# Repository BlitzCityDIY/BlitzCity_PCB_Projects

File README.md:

# BlitzCity_PCB_Projects
Projects with PCB files

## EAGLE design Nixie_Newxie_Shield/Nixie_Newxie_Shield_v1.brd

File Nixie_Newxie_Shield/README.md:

# Nixie Newxie Shield

A PCB that lets you plug four [Newxie Vertical Displays](https://www.adafruit.com/product/6113) into an Arduino/Metro format board.

It uses the 2x3 SPI pins on the edge of the board and pins 5-12 for CS and DC for each display.

Tested with an [Adafruit Metro ESP32-S3](https://www.adafruit.com/product/5500). Two Arduino examples are available:

* Color Test - Blinks a different color on each of the four displays (yellow, red, blue and green)
* Nixie Clock - Fetches the time from the [Worldtime API](http://worldtimeapi.org/api/timezone/Etc/UTC) and displays it using Nixie tube number images
	* The Nixie tube images are from [Wikimedia](https://commons.wikimedia.org/w/index.php?search=nixie+tube+Z566M&title=Special%3AMediaSearch&type=image). They were cropped, converted to bitmaps and converted to byte arrays with [image2cpp](https://javl.github.io/image2cpp/).

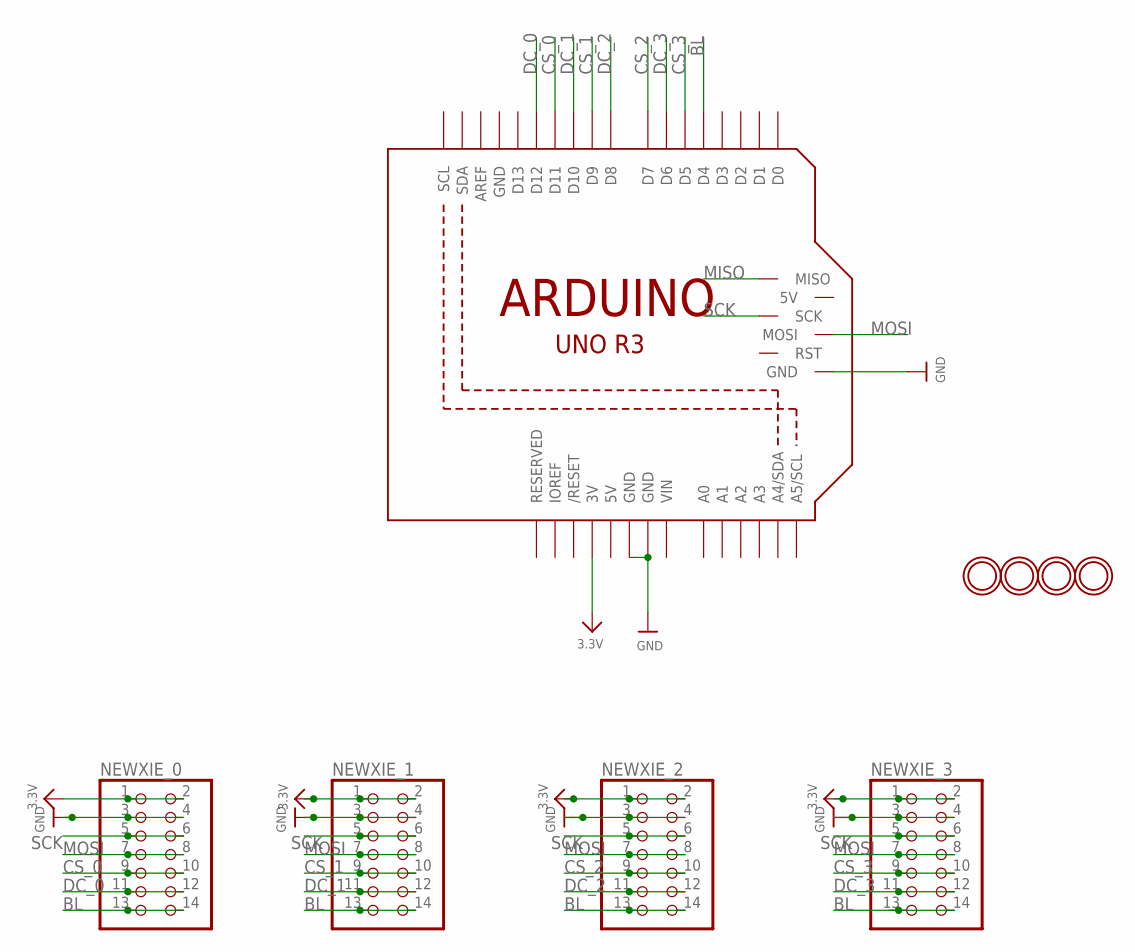
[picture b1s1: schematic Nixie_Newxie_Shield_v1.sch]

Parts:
NEWXIE_0, NEWXIE_1, NEWXIE_2, NEWXIE_3: HEADER-2X7; 2X07
U$12, U$13, U$14, U$15: MOUNTINGHOLE3.0_NPH; MOUNTINGHOLE_3.0_NPH
U$19: ARDUINO_R3_ICSP_NODIM; ARDUINOR3_ICSP_NODIM

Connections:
3.3V: NEWXIE_0.1, NEWXIE_0.2, NEWXIE_1.1, NEWXIE_1.2, NEWXIE_2.1, NEWXIE_2.2, NEWXIE_3.1, NEWXIE_3.2, U$19.3V
5V: U$19.5V
BL: NEWXIE_0.13, NEWXIE_0.14, NEWXIE_1.13, NEWXIE_1.14, NEWXIE_2.13, NEWXIE_2.14, NEWXIE_3.13, NEWXIE_3.14, U$19.D4
CS_0: NEWXIE_0.9, NEWXIE_0.10, U$19.D11
CS_1: NEWXIE_1.9, NEWXIE_1.10, U$19.D9
CS_2: NEWXIE_2.9, NEWXIE_2.10, U$19.D7
CS_3: NEWXIE_3.9, NEWXIE_3.10, U$19.D5
DC_0: NEWXIE_0.11, NEWXIE_0.12, U$19.D12
DC_1: NEWXIE_1.11, NEWXIE_1.12, U$19.D10
DC_2: NEWXIE_2.11, NEWXIE_2.12, U$19.D8
DC_3: NEWXIE_3.11, NEWXIE_3.12, U$19.D6
GND: NEWXIE_0.3, NEWXIE_0.4, NEWXIE_1.3, NEWXIE_1.4, NEWXIE_2.3, NEWXIE_2.4, NEWXIE_3.3, NEWXIE_3.4, U$19.GND, U$19.GND@1 (GND), U$19.GND@2 (GND), U$19.GND@3 (GND)
MISO: U$19.MISO
MOSI: NEWXIE_0.7, NEWXIE_0.8, NEWXIE_1.7, NEWXIE_1.8, NEWXIE_2.7, NEWXIE_2.8, NEWXIE_3.7, NEWXIE_3.8, U$19.MOSI
SCK: NEWXIE_0.5, NEWXIE_0.6, NEWXIE_1.5, NEWXIE_1.6, NEWXIE_2.5, NEWXIE_2.6, NEWXIE_3.5, NEWXIE_3.6, U$19.SCK
VIN: U$19.VIN

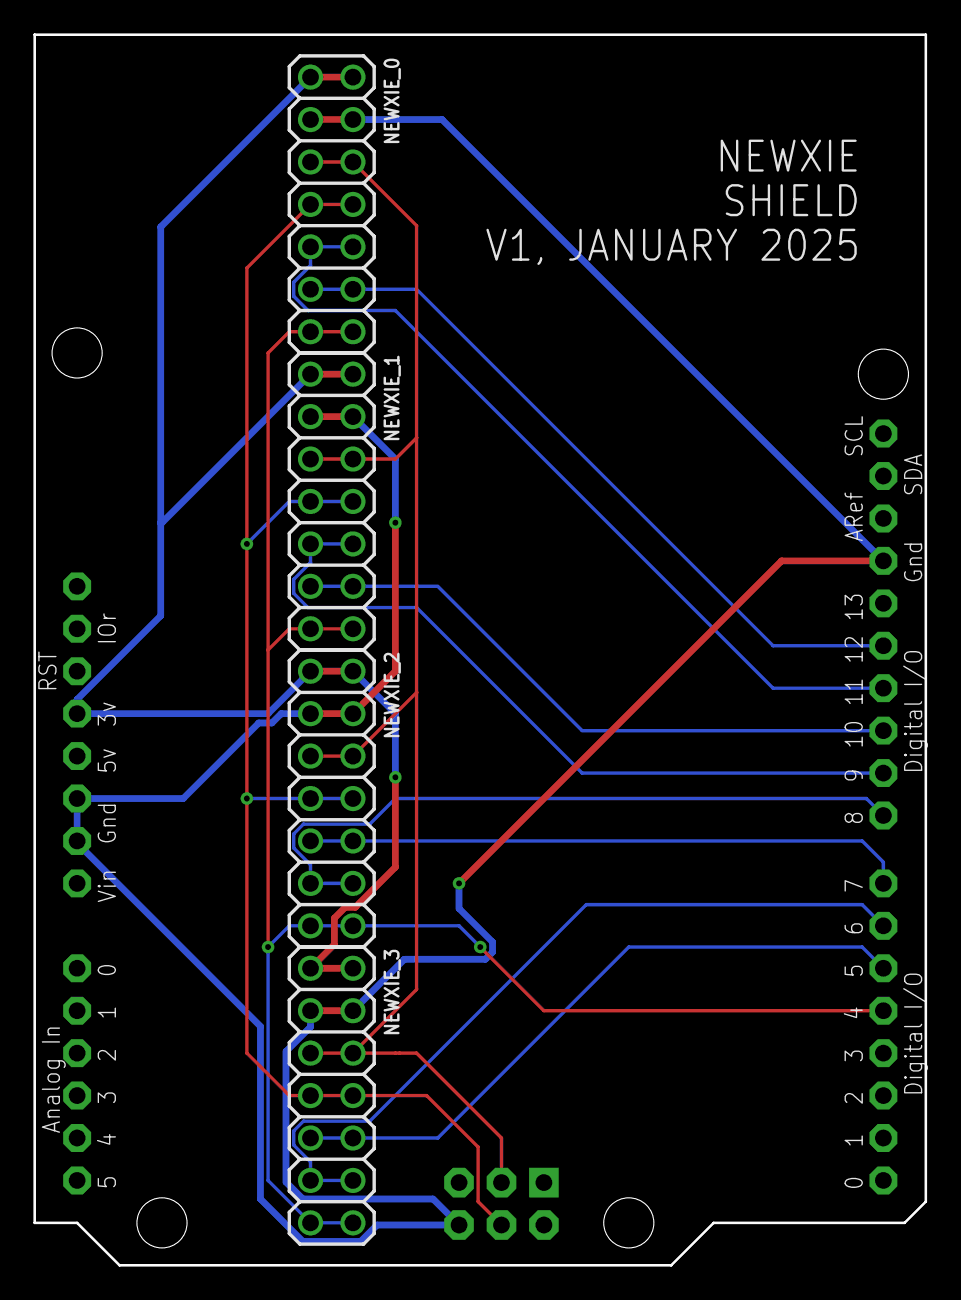
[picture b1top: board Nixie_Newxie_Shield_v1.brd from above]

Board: 2 copper layers, 53.3 x 73.7 mm, 9 parts (0 on the bottom side), 13 nets.

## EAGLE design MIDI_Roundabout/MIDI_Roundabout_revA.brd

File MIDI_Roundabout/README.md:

# MIDI Roundabout

A PCB that lets you route TRS-A, DIN-5 or TRS-B MIDI signals. It uses the MIDI Thru circuit with 220 ohm resistors on the two signal lines.

The switch is a [DP3T switch](https://www.digikey.com/en/products/detail/c-k/JS203011SCQN/7056055) that is available for PCBA on JLCPCB. The BOM and part placement files are available in the Gerber files folder.

Live demo video on [YouTube](https://www.youtube.com/live/Z-Sb5L-gl7c?si=7ahsuTD-HjMJuZga&t=2058)

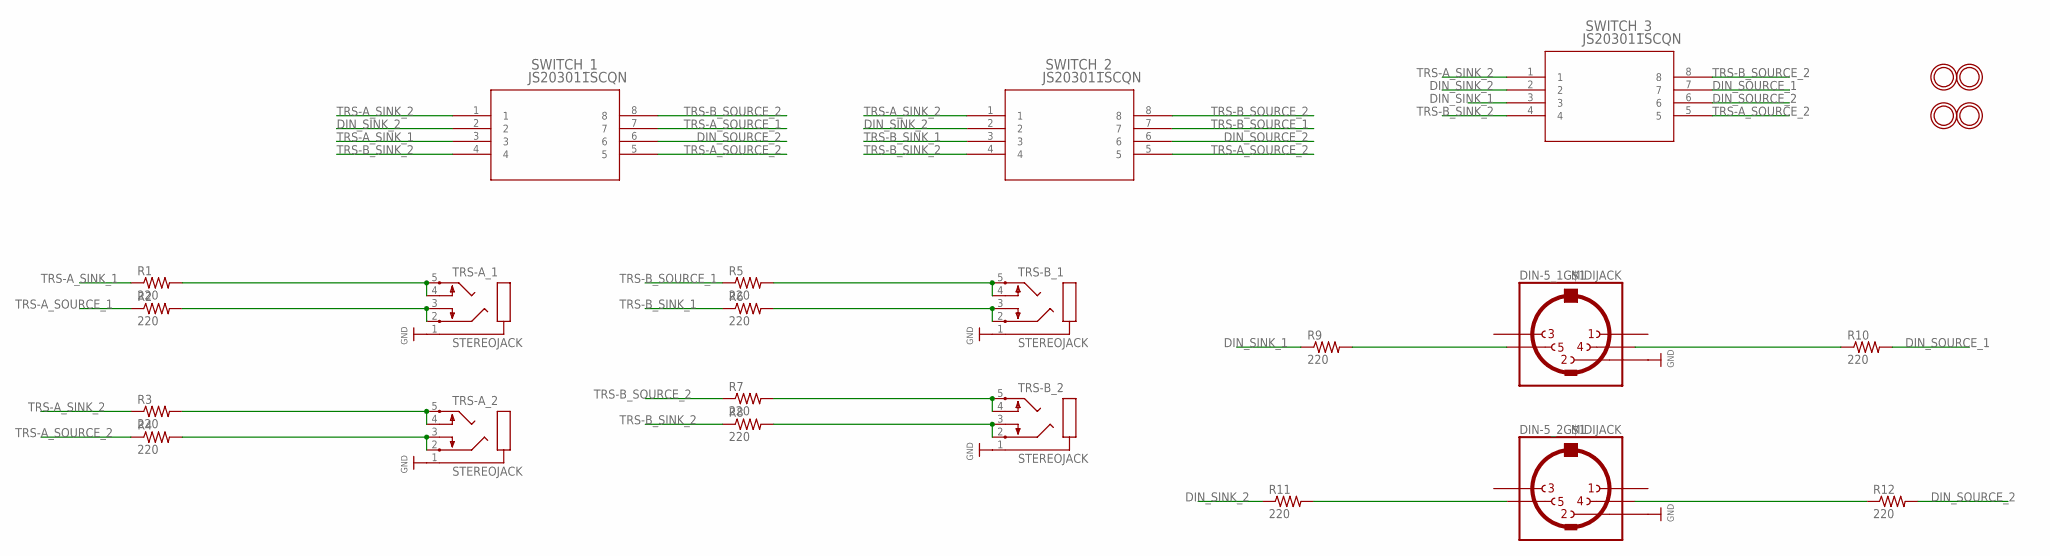
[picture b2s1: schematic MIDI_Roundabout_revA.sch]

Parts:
DIN-5_1, DIN-5_2: MIDIJACK; CP-2350
R1, R2, R3, R4, R5, R6, R7, R8, R9, R10, R11, R12: 220; R0805
SWITCH_1, SWITCH_2, SWITCH_3: JS203011SCQN; SWITCH_3011SCQN
TRS-A_1, TRS-A_2: STEREOJACK; STX3100
TRS-B_1, TRS-B_2: STEREOJACK; STX3100
U$7, U$8, U$9, U$10: MOUNTINGHOLE2.5_THICK; MOUNTINGHOLE_2.5_PLATED_THICK

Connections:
DIN_SINK_1: R9.1, SWITCH_3.3
DIN_SINK_2: R11.1, SWITCH_1.2, SWITCH_2.2, SWITCH_3.2
DIN_SOURCE_1: R10.2, SWITCH_3.7
DIN_SOURCE_2: R12.2, SWITCH_1.6, SWITCH_2.6, SWITCH_3.6
GND: DIN-5_1.2, DIN-5_2.2, TRS-A_1.1, TRS-A_2.1, TRS-B_1.1, TRS-B_2.1
unnamed: DIN-5_1.5, R9.2
unnamed: DIN-5_1.4, R10.1
unnamed: DIN-5_2.4, R12.1
unnamed: DIN-5_2.5, R11.2
unnamed: R1.2, TRS-A_1.4, TRS-A_1.5
unnamed: R2.2, TRS-A_1.2, TRS-A_1.3
unnamed: R3.2, TRS-A_2.4, TRS-A_2.5
unnamed: R4.2, TRS-A_2.2, TRS-A_2.3
unnamed: R5.2, TRS-B_1.4, TRS-B_1.5
unnamed: R6.2, TRS-B_1.2, TRS-B_1.3
unnamed: R7.2, TRS-B_2.4, TRS-B_2.5
unnamed: R8.2, TRS-B_2.2, TRS-B_2.3
TRS-A_SINK_1: R1.1, SWITCH_1.3
TRS-A_SINK_2: R3.1, SWITCH_1.1, SWITCH_2.1, SWITCH_3.1
TRS-A_SOURCE_1: R2.1, SWITCH_1.7
TRS-A_SOURCE_2: R4.1, SWITCH_1.5, SWITCH_2.5, SWITCH_3.5
TRS-B_SINK_1: R6.1, SWITCH_2.3
TRS-B_SINK_2: R8.1, SWITCH_1.4, SWITCH_2.4, SWITCH_3.4
TRS-B_SOURCE_1: R5.1, SWITCH_2.7
TRS-B_SOURCE_2: R7.1, SWITCH_1.8, SWITCH_2.8, SWITCH_3.8

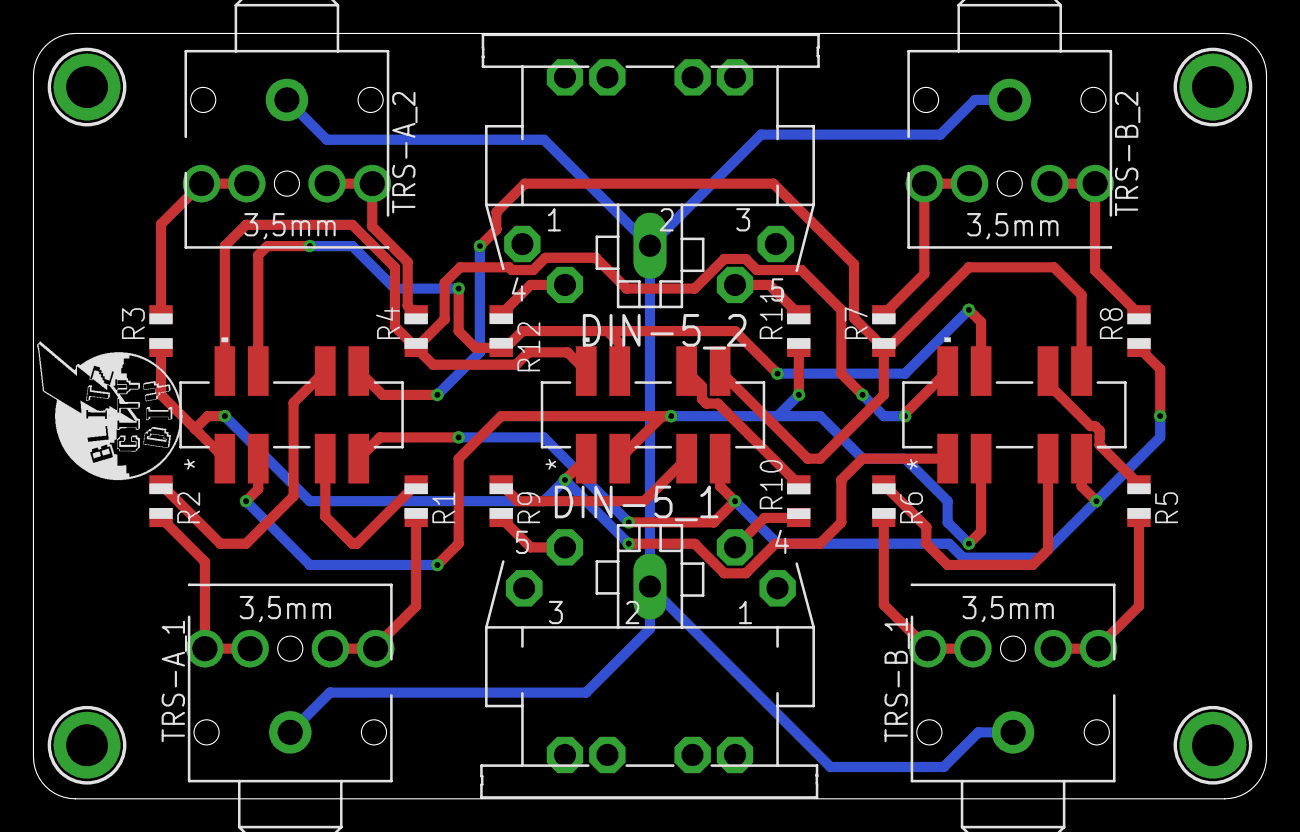
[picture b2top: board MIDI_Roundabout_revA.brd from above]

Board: 2 copper layers, 73.7 x 45.7 mm, 45 parts (0 on the bottom side), 25 nets.

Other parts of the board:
PLABEL200: PLABEL200
PLABEL201: PLABEL201
PLABEL202: PLABEL202
PLABEL203: PLABEL203
PLABEL204: PLABEL204
PLABEL205: PLABEL205
PLABEL206: PLABEL206
PLABEL207: PLABEL207
PLABEL208: PLABEL208
PLABEL209: PLABEL209
PLABEL210: PLABEL210
PLABEL211: PLABEL211
PLABEL212: PLABEL212
PLABEL213: PLABEL213
PLABEL214: PLABEL214
PLABEL215: PLABEL215
PLABEL216: PLABEL216
PLABEL217: PLABEL217
PLABEL218: PLABEL218
PLABEL219: PLABEL219

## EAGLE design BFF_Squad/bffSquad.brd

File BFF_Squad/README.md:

# BFF Squad

A carrier PCB that lets you use multiple QT Py BFF breakout boards with a QT Py without having to stack them vertically. 

This is a bit of a hack, make sure you check that the BFF's you're using aren't sharing important pins.

Shared on [OSHPark](https://oshpark.com/shared_projects/5sXhVjRq)

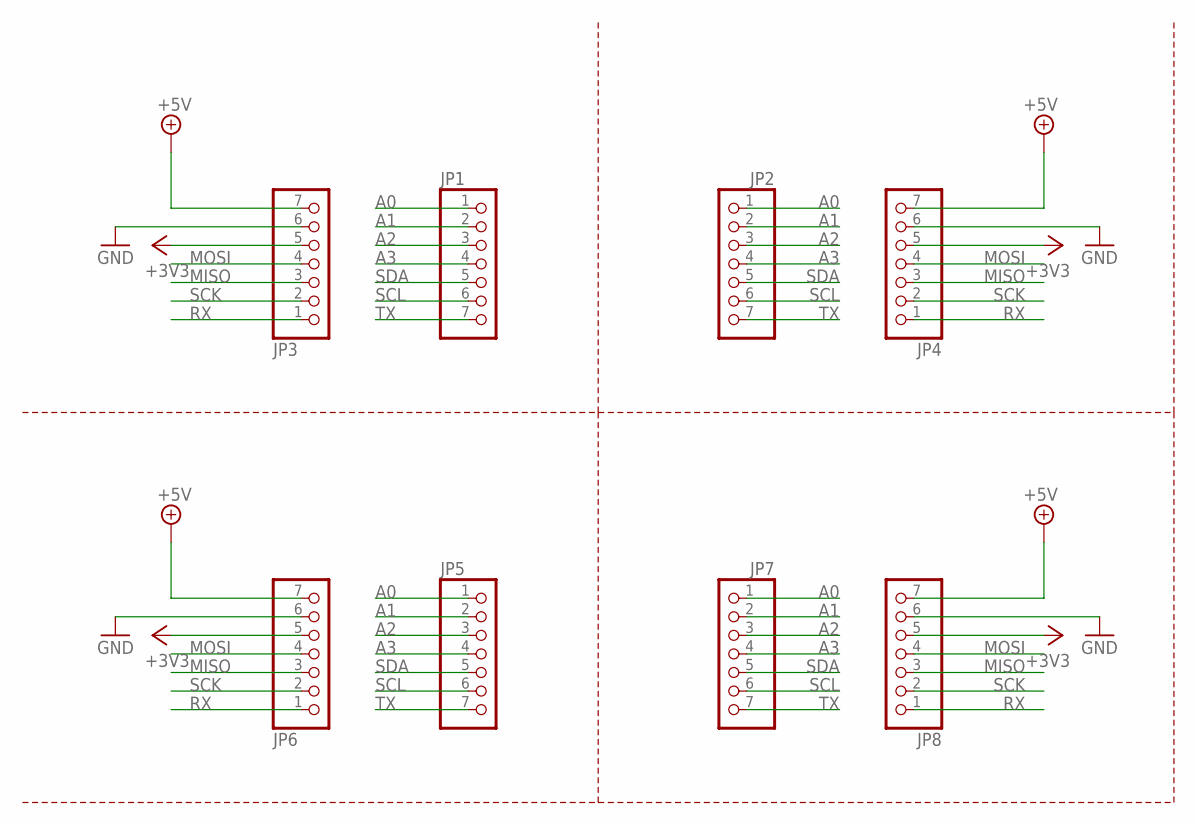
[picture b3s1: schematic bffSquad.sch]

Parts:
JP1, JP2, JP3, JP4, JP5, JP6, JP7, JP8: HEADER-1X7ROUND; 1X07_ROUND

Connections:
+3V3: JP3.5, JP4.5, JP6.5, JP8.5
+5V: JP3.7, JP4.7, JP6.7, JP8.7
A0: JP1.1, JP2.1, JP5.1, JP7.1
A1: JP1.2, JP2.2, JP5.2, JP7.2
A2: JP1.3, JP2.3, JP5.3, JP7.3
A3: JP1.4, JP2.4, JP5.4, JP7.4
GND: JP3.6, JP4.6, JP6.6, JP8.6
MISO: JP3.3, JP4.3, JP6.3, JP8.3
MOSI: JP3.4, JP4.4, JP6.4, JP8.4
RX: JP3.1, JP4.1, JP6.1, JP8.1
SCK: JP3.2, JP4.2, JP6.2, JP8.2
SCL: JP1.6, JP2.6, JP5.6, JP7.6
SDA: JP1.5, JP2.5, JP5.5, JP7.5
TX: JP1.7, JP2.7, JP5.7, JP7.7

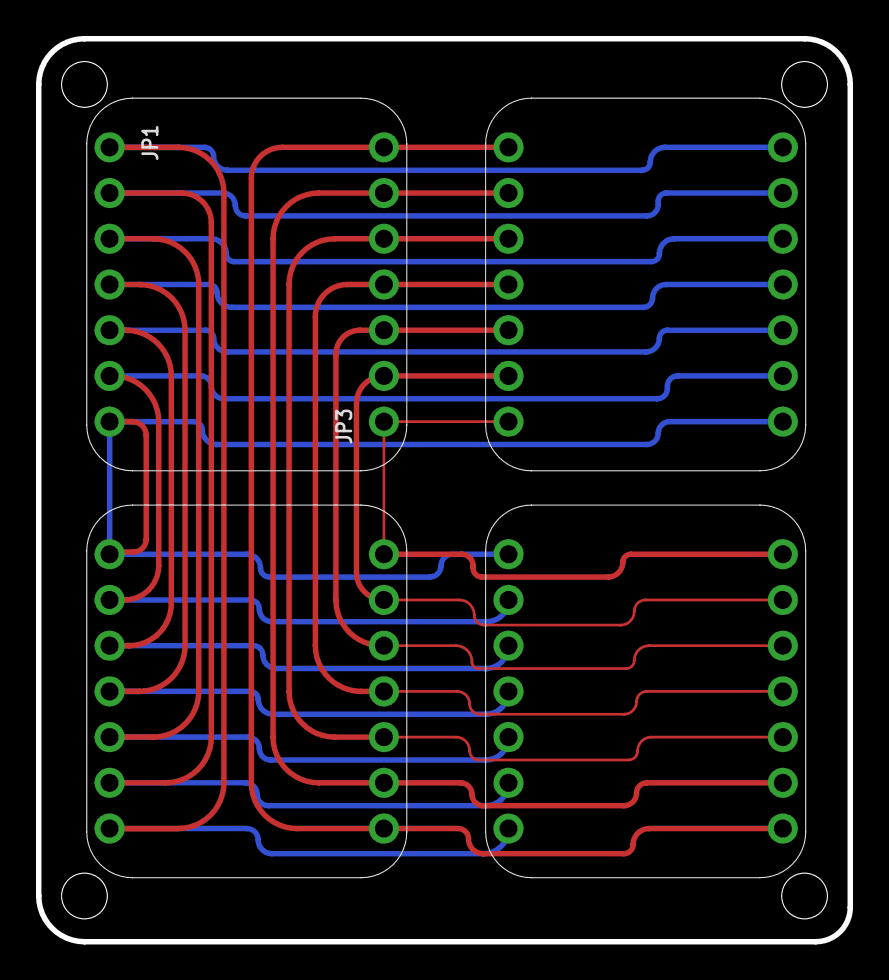
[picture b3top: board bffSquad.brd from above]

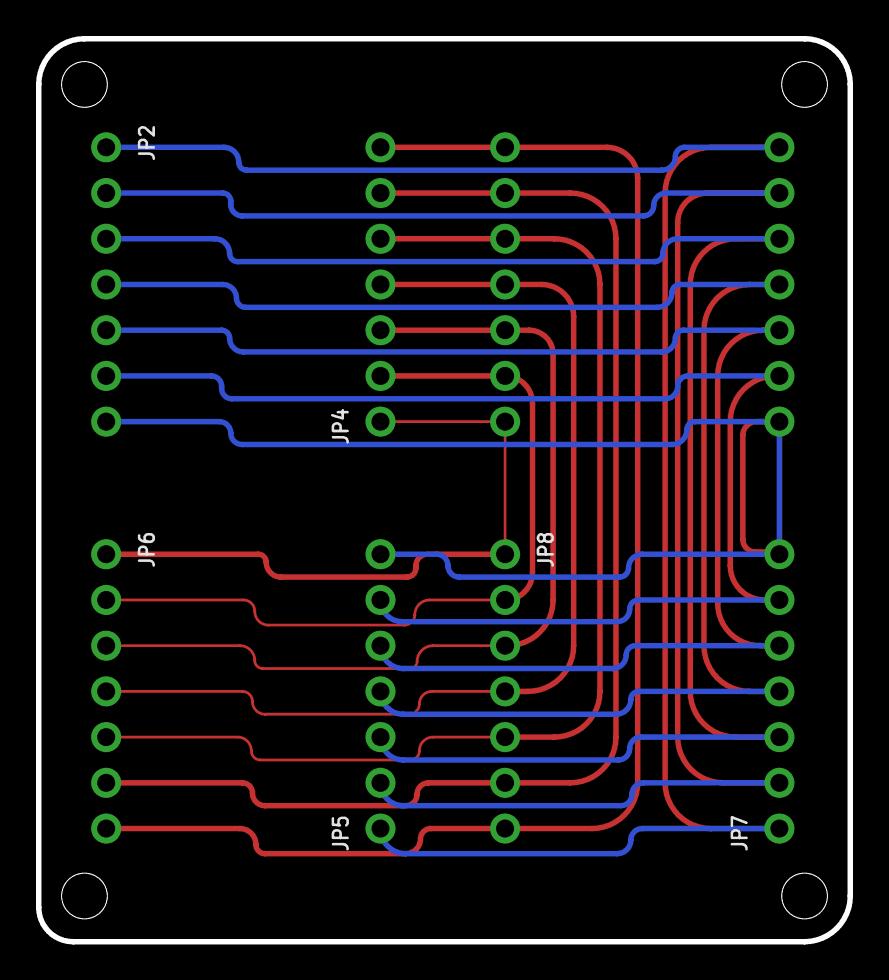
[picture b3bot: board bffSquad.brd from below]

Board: 2 copper layers, 45.1 x 50.2 mm, 27 parts (9 on the bottom side), 14 nets.

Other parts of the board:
PLABEL0: PLABEL0
PLABEL1: PLABEL1
PLABEL2: PLABEL2
PLABEL3: PLABEL3
PLABEL4: PLABEL4
PLABEL5: PLABEL5
PLABEL6: PLABEL6
PLABEL7: PLABEL7
PLABEL8: PLABEL8
PLABEL9: PLABEL9
PLABEL10: PLABEL10
PLABEL11: PLABEL11
PLABEL12: PLABEL12
PLABEL13: PLABEL13
PLABEL14: PLABEL14
PLABEL15: PLABEL15
PLABEL16: PLABEL16
PLABEL17: PLABEL17
PLABEL18: PLABEL18

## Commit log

2025-06-06 adding pocket operator files
2025-06-06 excel to csv
2025-06-06 Update code.py
    license
2025-06-06 Create LICENSE
    MIT
2025-06-20 adding bff squad
2025-06-23 add midi roundabout
2025-06-30 adding nixie newxie shield
2025-07-01 comment out serial port wait
2025-11-25 adding pi pc files
2025-11-25 Update README.md with external links
    Added external links section with Printables download.
2026-04-30 kicad part, encoder project
2026-04-30 gitignore
2026-05-06 encoder breakout rev a
2026-05-06 gitignore cleanup

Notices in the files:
parts and their libraries:
microbuilder: This work is placed in the public domain, and may be freely used for commercial and non-commercial work with the following conditions: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
COPYRIGHT: Copyright (C) 2025 Ultra Librarian. All rights reserved.
